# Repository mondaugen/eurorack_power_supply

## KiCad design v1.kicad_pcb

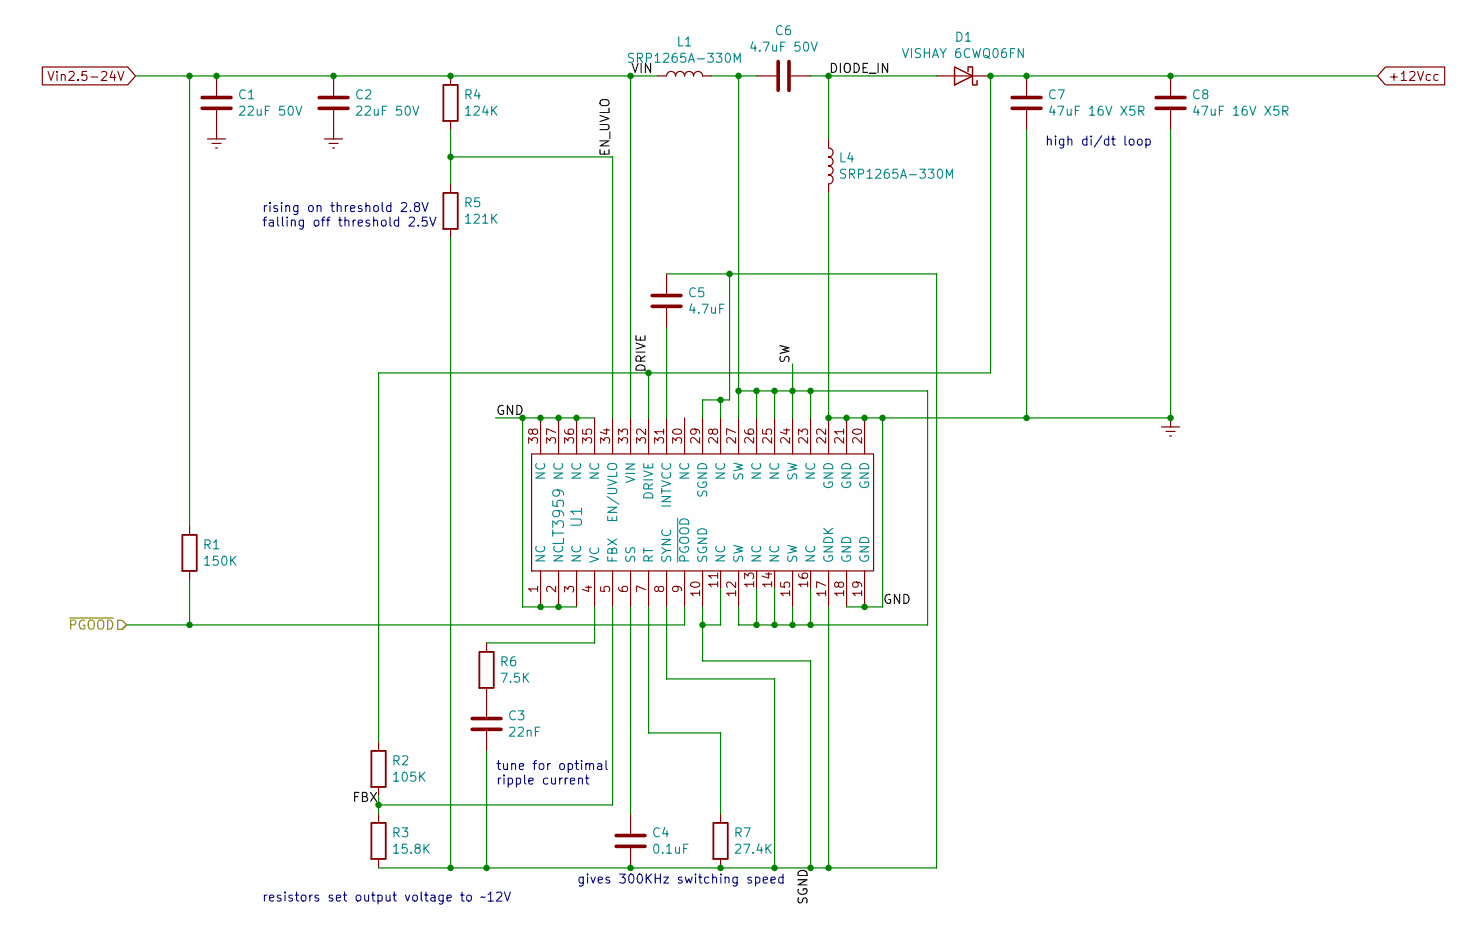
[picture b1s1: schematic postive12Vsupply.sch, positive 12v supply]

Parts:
C1, C2: 22uF 50V; C_0805_2012Metric_Pad1.15x1.40mm_HandSolder
C3: 22nF; C_0805_2012Metric_Pad1.15x1.40mm_HandSolder
C4: 0.1uF; C_0805_2012Metric_Pad1.15x1.40mm_HandSolder
C5: 4.7uF; C_0805_2012Metric_Pad1.15x1.40mm_HandSolder
C6: 4.7uF 50V; C_0805_2012Metric_Pad1.15x1.40mm_HandSolder
C7, C8: 47uF 16V X5R; C_0805_2012Metric_Pad1.15x1.40mm_HandSolder
D1: VISHAY 6CWQ06FN
L1, L4: SRP1265A-330M; bourns_srp1265a
R1: 150K; R_0805_2012Metric_Pad1.15x1.40mm_HandSolder
R2: 105K; R_0805_2012Metric_Pad1.15x1.40mm_HandSolder
R3: 15.8K; R_0805_2012Metric_Pad1.15x1.40mm_HandSolder
R4: 124K; R_0805_2012Metric_Pad1.15x1.40mm_HandSolder
R5: 121K; R_0805_2012Metric_Pad1.15x1.40mm_HandSolder
R6: 7.5K; R_0805_2012Metric_Pad1.15x1.40mm_HandSolder
R7: 27.4K; R_0805_2012Metric_Pad1.15x1.40mm_HandSolder
U1: LT3959; lt3959_TSSOP-38

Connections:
+12Vcc: C7.1, C8.1, D1.1 (K), R2.1, U1.32 (DRIVE); also elsewhere on the board
/positive 12V supply/DIODE_IN: C6.2, D1.2 (A), L4.1
/positive 12V supply/EN_UVLO: R4.2, R5.1, U1.34 (EN/UVLO)
/positive 12V supply/FBX: R2.2, R3.1, U1.5 (FBX)
/positive 12V supply/SGND: C3.2, C4.2, C5.1, R3.2, R5.2, R7.2, U1.8 (SYNC), U1.10 (SGND), U1.11 (NC), U1.17 (GNDK), U1.28 (NC), U1.29 (SGND)
/positive 12V supply/SW: C6.1, L1.2, U1.12 (SW), U1.13 (NC), U1.14 (NC), U1.15 (SW), U1.16 (NC), U1.23 (NC), U1.24 (SW), U1.25 (NC), U1.26 (NC), U1.27 (SW)
/positive 12V supply/~PGOOD: R1.2, U1.9 (~PGOOD); also elsewhere on the board
Earth: C1.2, C2.2, C7.2, C8.2, L4.2, U1.1 (NC), U1.2 (NC), U1.3 (NC), U1.18 (GND), U1.19 (GND), U1.20 (GND), U1.21 (GND), U1.22 (GND), U1.35 (NC), U1.36 (NC), U1.37 (NC), U1.38 (NC); also elsewhere on the board
unnamed: C3.1, R6.2
unnamed: C4.1, U1.6 (SS)
unnamed: C5.2, U1.31 (INTVCC)
unnamed: R6.1, U1.4 (VC)
unnamed: R7.1, U1.7 (RT)
Vin2.5-24V: C1.1, C2.1, L1.1, R1.1, R4.1, U1.33 (VIN); also elsewhere on the board

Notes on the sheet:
gives 300KHz switching speed
tune for optimal ripple current
rising on threshold 2.8V falling off threshold 2.5V
resistors set output voltage to ~~12V
high di/dt loop

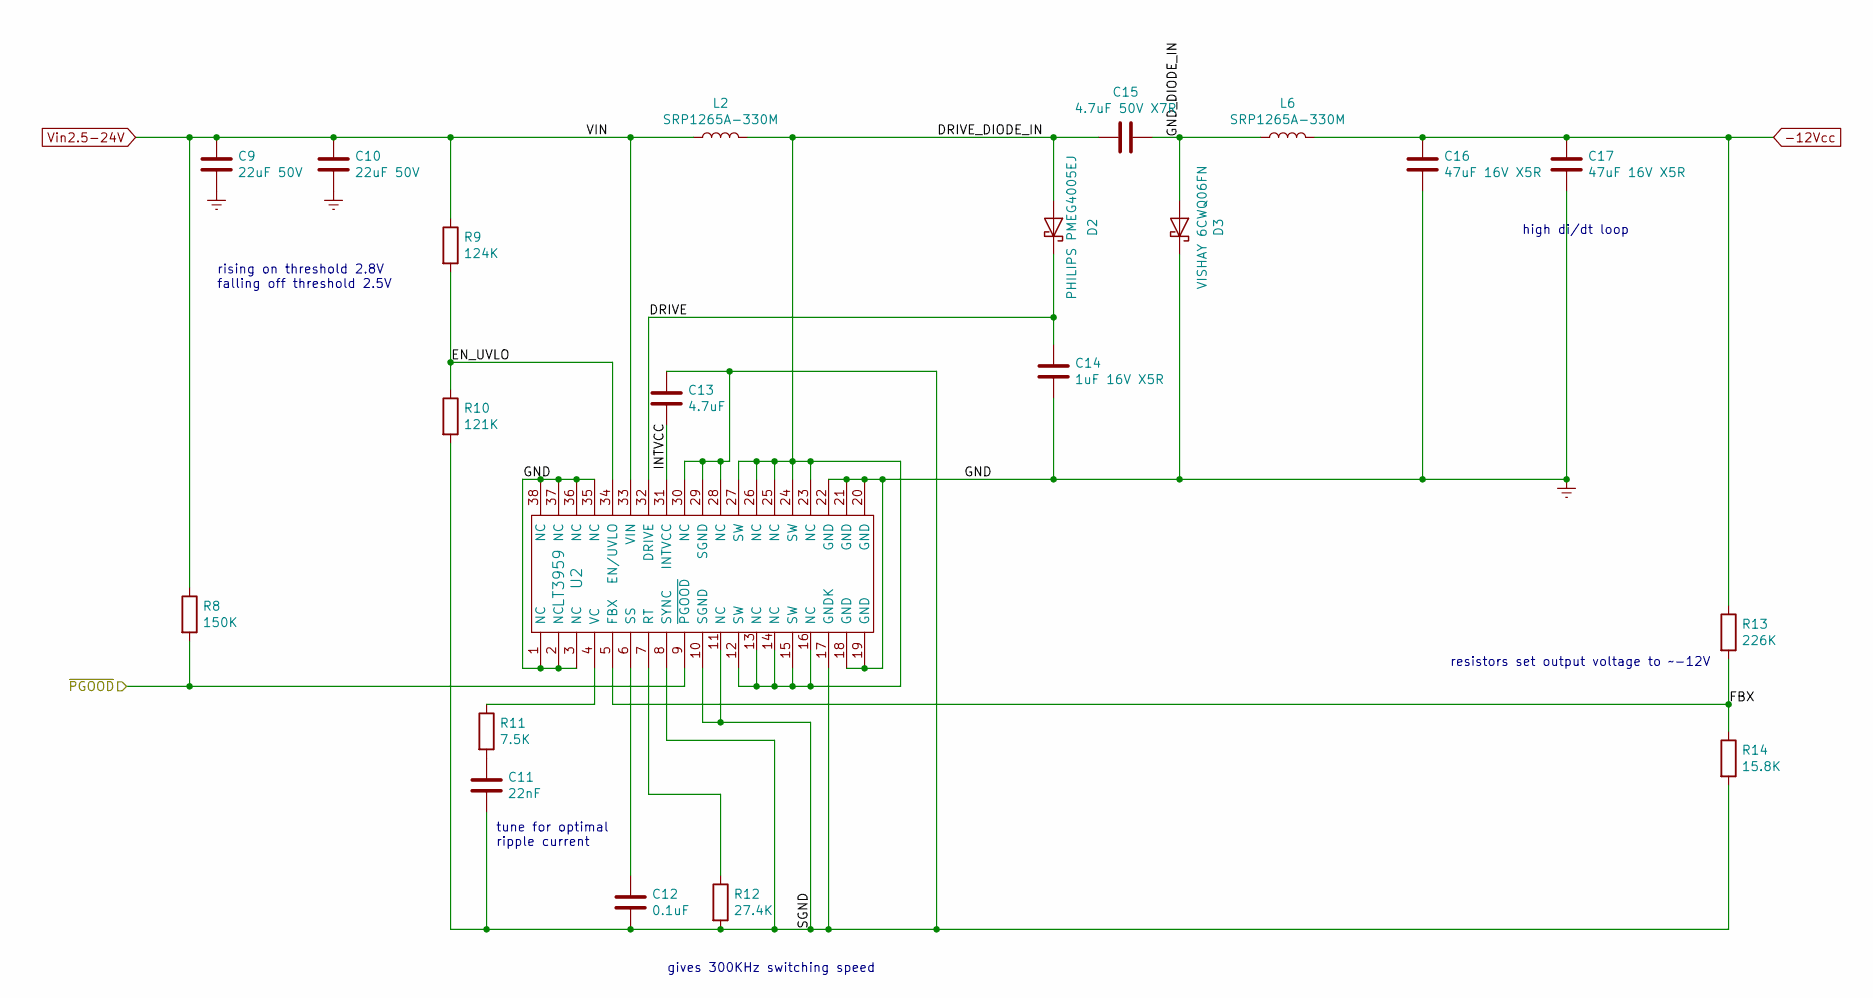
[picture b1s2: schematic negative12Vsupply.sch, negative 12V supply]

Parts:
C9, C10: 22uF 50V; C_0805_2012Metric_Pad1.15x1.40mm_HandSolder
C11: 22nF; C_0805_2012Metric_Pad1.15x1.40mm_HandSolder
C12: 0.1uF; C_0805_2012Metric_Pad1.15x1.40mm_HandSolder
C13: 4.7uF; C_0805_2012Metric_Pad1.15x1.40mm_HandSolder
C14: 1uF 16V X5R; C_0805_2012Metric_Pad1.15x1.40mm_HandSolder
C15: 4.7uF 50V X7R; C_0805_2012Metric_Pad1.15x1.40mm_HandSolder
C16, C17: 47uF 16V X5R; C_0805_2012Metric_Pad1.15x1.40mm_HandSolder
D2: PHILIPS PMEG4005EJ; D_SOD-123
D3: VISHAY 6CWQ06FN; TO-252-2
L2, L6: SRP1265A-330M; bourns_srp1265a
R8: 150K; R_0805_2012Metric_Pad1.15x1.40mm_HandSolder
R9: 124K; R_0805_2012Metric_Pad1.15x1.40mm_HandSolder
R10: 121K; R_0805_2012Metric_Pad1.15x1.40mm_HandSolder
R11: 7.5K; R_0805_2012Metric_Pad1.15x1.40mm_HandSolder
R12: 27.4K; R_0805_2012Metric_Pad1.15x1.40mm_HandSolder
R13: 226K; R_0805_2012Metric_Pad1.15x1.40mm_HandSolder
R14: 15.8K; R_0805_2012Metric_Pad1.15x1.40mm_HandSolder
U2: LT3959; lt3959_TSSOP-38

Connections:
-12Vcc: C16.1, C17.1, L6.2, R13.1; also elsewhere on the board
/negative 12V supply/DRIVE: C14.1, D2.1 (K), U2.32 (DRIVE)
/negative 12V supply/DRIVE_DIODE_IN: C15.1, D2.2 (A), L2.2, U2.12 (SW), U2.13 (NC), U2.14 (NC), U2.15 (SW), U2.16 (NC), U2.23 (NC), U2.24 (SW), U2.25 (NC), U2.26 (NC), U2.27 (SW)
/negative 12V supply/EN_UVLO: R9.2, R10.1, U2.34 (EN/UVLO)
/negative 12V supply/FBX: R13.2, R14.1, U2.5 (FBX)
/negative 12V supply/GND_DIODE_IN: C15.2, D3.2 (A), L6.1
/negative 12V supply/INTVCC: C13.2, U2.31 (INTVCC)
/negative 12V supply/SGND: C11.2, C12.2, C13.1, R10.2, R12.2, R14.2, U2.8 (SYNC), U2.10 (SGND), U2.11 (NC), U2.17 (GNDK), U2.28 (NC), U2.29 (SGND), U2.30 (NC)
/negative 12V supply/~PGOOD: R8.2, U2.9 (~PGOOD); also elsewhere on the board
Earth: C9.2, C10.2, C14.2, C16.2, C17.2, D3.1 (K), U2.1 (NC), U2.2 (NC), U2.3 (NC), U2.18 (GND), U2.19 (GND), U2.20 (GND), U2.21 (GND), U2.22 (GND), U2.35 (NC), U2.36 (NC), U2.37 (NC), U2.38 (NC); also elsewhere on the board
unnamed: C11.1, R11.2
unnamed: C12.1, U2.6 (SS)
unnamed: R11.1, U2.4 (VC)
unnamed: R12.1, U2.7 (RT)
Vin2.5-24V: C9.1, C10.1, L2.1, R8.1, R9.1, U2.33 (VIN); also elsewhere on the board

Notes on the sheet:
resistors set output voltage to ~~-12V
tune for optimal ripple current
gives 300KHz switching speed
high di/dt loop
rising on threshold 2.8V falling off threshold 2.5V

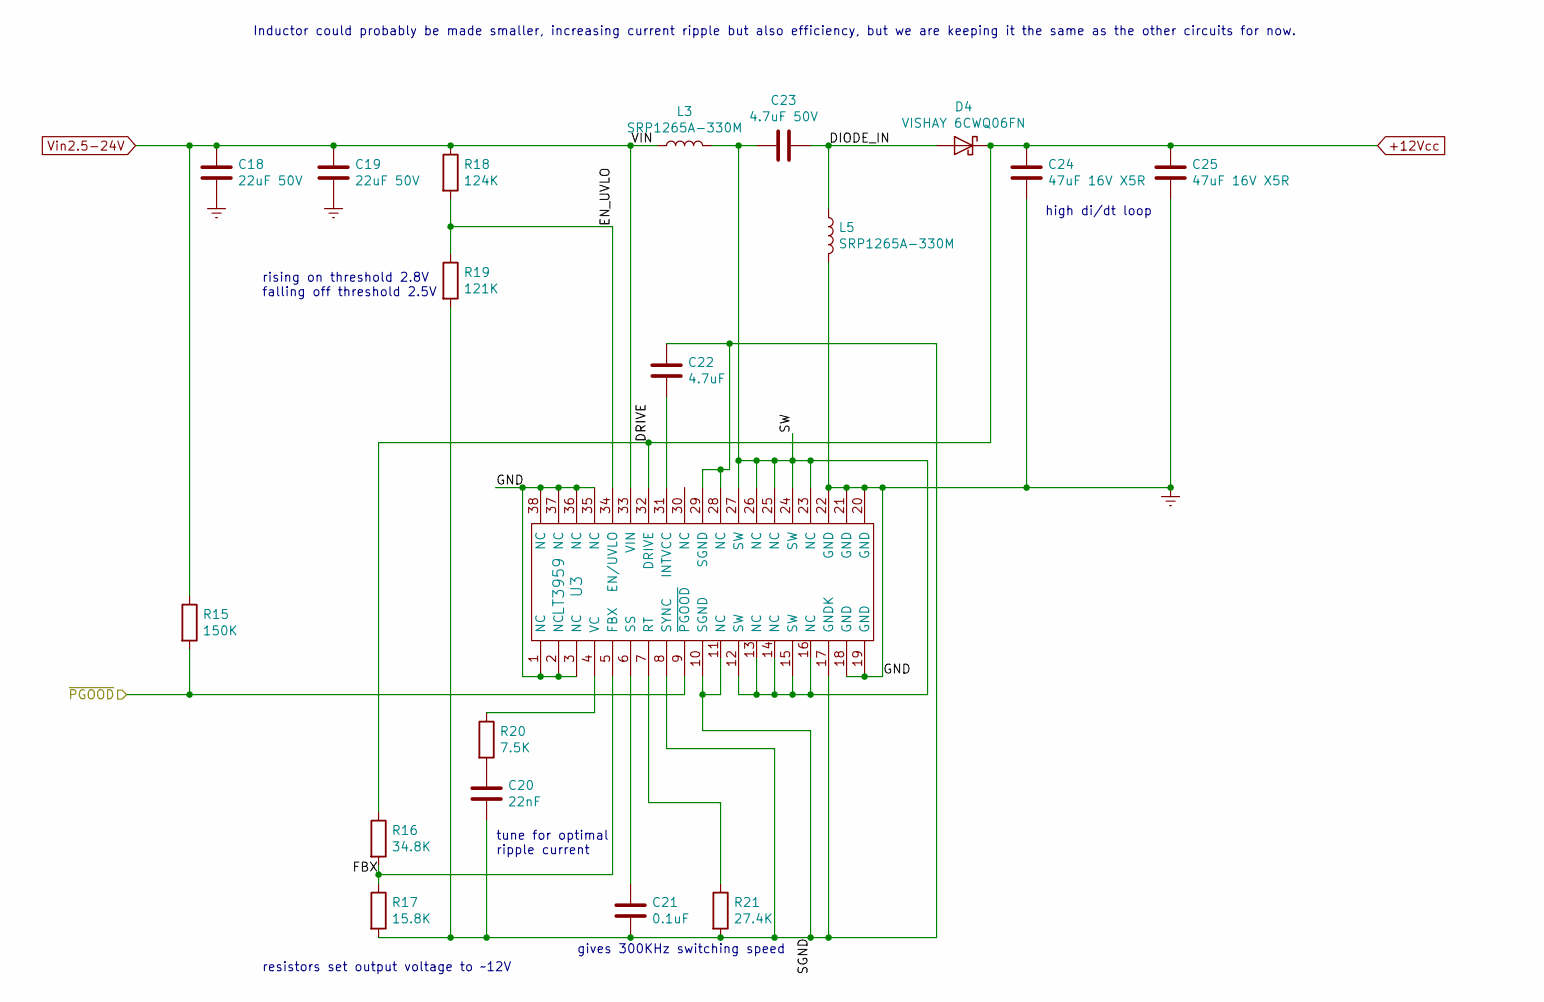
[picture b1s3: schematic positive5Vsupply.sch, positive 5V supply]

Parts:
C18, C19: 22uF 50V; C_0805_2012Metric_Pad1.15x1.40mm_HandSolder
C20: 22nF; C_0805_2012Metric_Pad1.15x1.40mm_HandSolder
C21: 0.1uF; C_0805_2012Metric_Pad1.15x1.40mm_HandSolder
C22: 4.7uF; C_0805_2012Metric_Pad1.15x1.40mm_HandSolder
C23: 4.7uF 50V; C_0805_2012Metric_Pad1.15x1.40mm_HandSolder
C24, C25: 47uF 16V X5R; C_0805_2012Metric_Pad1.15x1.40mm_HandSolder
D4: VISHAY 6CWQ06FN; TO-252-2
L3, L5: SRP1265A-330M; bourns_srp1265a
R15: 150K; R_0805_2012Metric_Pad1.15x1.40mm_HandSolder
R16: 34.8K; R_0805_2012Metric_Pad1.15x1.40mm_HandSolder
R17: 15.8K; R_0805_2012Metric_Pad1.15x1.40mm_HandSolder
R18: 124K; R_0805_2012Metric_Pad1.15x1.40mm_HandSolder
R19: 121K; R_0805_2012Metric_Pad1.15x1.40mm_HandSolder
R20: 7.5K; R_0805_2012Metric_Pad1.15x1.40mm_HandSolder
R21: 27.4K; R_0805_2012Metric_Pad1.15x1.40mm_HandSolder
U3: LT3959; lt3959_TSSOP-38

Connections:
+12Vcc: C24.1, C25.1, D4.1 (K), R16.1, U3.32 (DRIVE); also elsewhere on the board
/positive5Vsupply/DIODE_IN: C23.2, D4.2 (A), L5.1
/positive5Vsupply/EN_UVLO: R18.2, R19.1, U3.34 (EN/UVLO)
/positive5Vsupply/FBX: R16.2, R17.1, U3.5 (FBX)
/positive5Vsupply/SGND: C20.2, C21.2, C22.1, R17.2, R19.2, R21.2, U3.8 (SYNC), U3.10 (SGND), U3.11 (NC), U3.17 (GNDK), U3.28 (NC), U3.29 (SGND)
/positive5Vsupply/SW: C23.1, L3.2, U3.12 (SW), U3.13 (NC), U3.14 (NC), U3.15 (SW), U3.16 (NC), U3.23 (NC), U3.24 (SW), U3.25 (NC), U3.26 (NC), U3.27 (SW)
/positive5Vsupply/~PGOOD: R15.2, U3.9 (~PGOOD); also elsewhere on the board
Earth: C18.2, C19.2, C24.2, C25.2, L5.2, U3.1 (NC), U3.2 (NC), U3.3 (NC), U3.18 (GND), U3.19 (GND), U3.20 (GND), U3.21 (GND), U3.22 (GND), U3.35 (NC), U3.36 (NC), U3.37 (NC), U3.38 (NC); also elsewhere on the board
unnamed: C20.1, R20.2
unnamed: C21.1, U3.6 (SS)
unnamed: C22.2, U3.31 (INTVCC)
unnamed: R20.1, U3.4 (VC)
unnamed: R21.1, U3.7 (RT)
Vin2.5-24V: C18.1, C19.1, L3.1, R15.1, R18.1, U3.33 (VIN); also elsewhere on the board

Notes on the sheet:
Inductor could probably be made smaller, increasing current ripple but also efficiency, but we are keeping it the same as the other circuits for now.
gives 300KHz switching speed
tune for optimal ripple current
rising on threshold 2.8V falling off threshold 2.5V
resistors set output voltage to ~~12V
high di/dt loop

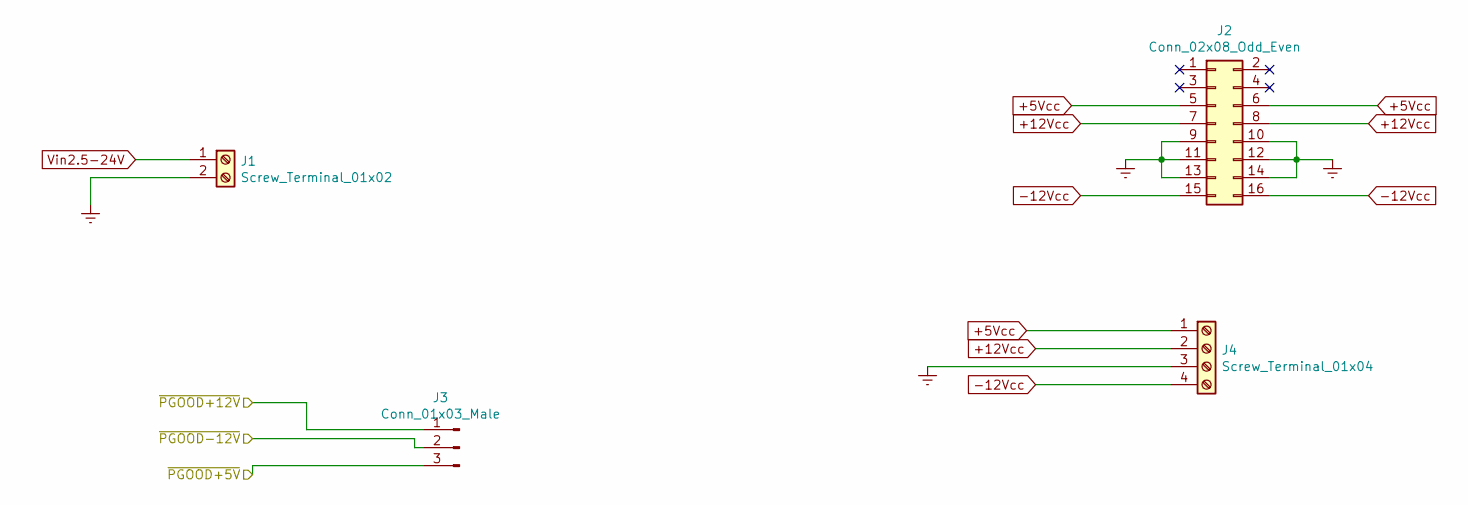
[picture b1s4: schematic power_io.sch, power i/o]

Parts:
J1: Screw_Terminal_01x02; wuerth_3117_5.00mm_691311700102
J2: Conn_02x08_Odd_Even; PinHeader_2x08_P2.54mm_Vertical
J3: Conn_01x03_Male; PinHeader_1x03_P2.54mm_Vertical
J4: Screw_Terminal_01x04; wuerth_1337_1x4_5.00mm_691137710004

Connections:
+5Vcc: J2.5, J2.6, J4.1
+12Vcc: J2.7, J2.8, J4.2; also elsewhere on the board
-12Vcc: J2.15, J2.16, J4.4; also elsewhere on the board
/negative 12V supply/~PGOOD: J3.2; also elsewhere on the board
/positive5Vsupply/~PGOOD: J3.3; also elsewhere on the board
/positive 12V supply/~PGOOD: J3.1; also elsewhere on the board
Earth: J1.2, J2.9, J2.10, J2.11, J2.12, J2.13, J2.14, J4.3; also elsewhere on the board
Vin2.5-24V: J1.1; also elsewhere on the board

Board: 4 copper layers, 63 parts (0 on the bottom side), 39 nets, no tracks yet.

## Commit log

2019-04-03 Added split inductor symbol
    Schematic easier to follow now
2019-04-08 Added footprints, starting layout
2019-04-09 Started laying out
    shared inductor is a pain, so we're splitting into 2
2019-04-09 Named nets, made it use 2 inductors
2019-04-11 Layed out inductors,
    Now just have to lay out resistors that configure the power supply
2019-04-11 Use better footprint for TO-252 diode package
